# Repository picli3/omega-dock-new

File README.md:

# Omega dock\new con rele de estado solido a 220v @ 1A

Project released under CC-BY-SA 4.0 license  

1. [Project status](#project-status)  
1. [Project description](#project-description)  
1. [BOM](#bom)  
1. [Photos](#photos) 

If you want to discuss the project, join [the thread in the onion community forum](https://community.onion.io/topic/2284/my-omega-2-2-dock-new)

## Project status
v0.9 tested, working with some bodges  
v1.0 boards not tested yet, **proceed at your own risk**

## Project description 
This is my dock\new project: it's a small dock (same size as the mini dock and the omega) for the Onion Omega 2 and 2+.

I needed the smallest dock i could do, that featured:

* Ethernet
* Type A USB host
* Micro USB for power

It has an onboard linear voltage regulation (i didn't bother going with a switching one for such low power), magnetics integrated in the RJ45 connector to save space, USB host ESD protection (diode array), USB host PTC fuse.

On the left side there is the RJ45 connector and nothing on the back side of the board, so that you can easily access the MicroSD card on the Omega 2+.
On the right side (the antenna side of the omega) you have the USB type A connector, facing outwards, and the microusb connector for power, facing inwards.

The first version, v0.9, had some issues with the ethernet. Currently i've released v1.0 that solves all the issues, adds a led to check power and, making a better use of the space, the RJ45 connector doesn't protrude anymore. I haven't ordered the v1.0 PCBs yet, but the circuit is tested.

I've chosen 0805 passives, 1206 ptc fuse, big smd electrolitic caps, a SOT223 (the classic 1117) for power regulation and a SOT23-6 for usb host protection, so it can all be easily handsoldered with just a plain soldering iron. Probably the hardest part to handsolder is the SOT23-6 but it's easily doable by hand.

The components and board cost for the prototype it's arround 10 to 15€ per board.

## BOM
|    Symbol   |                 Package                | Quantity |    Valore   |                          Note                          |
|:-----------:|:--------------------------------------:|:--------:|:-----------:|:------------------------------------------------------:|
| C1          | CP_Elec_4x5.3                          |     1    | 10uF        | 10V or higher                                          |
| C2          | CP_Elec_6.3x5.3                        |     1    | 100uF       | 10V or higher                                          |
| C3, C4      | 0805                                   |     2    | 100nF       |                                                        |
| C5          | 0805                                   |     1    | 1uF         |                                                        |
| D1          | 1206                                   |     1    | PWR         | Amber LED                                              |
| F1          | 1206                                   |     1    | 1.5A        | PTC Fuse                                               |
| J1          | USB_A                                  |     1    | USB_A       | MOLEX 67643-3910                                       |
| J2          | USB_Micro-B                            |     1    | USB_PWR     | ADAM TECH MCR-AB1-S-RA-SMT-CS1-TR                      |
| J3          | RJ45_TRAFO_AMPHENOL                    |     1    | RJ45-TRAFO  | AMPHENOL LMJ1598824110DT39                             |
| R1,R2,R3,R4 | 0805                                   |     4    | 50R         | Ethernet termination resistors: should be 1% or better |
| R5          | 0805                                   |     1    | 150R        |                                                        |
| U1          | SOT23-6                                |     1    | USBLC6-2SC6 |                                                        |
| U2          | SOT223                                 |     1    | AP111733    |                                                        |
| U3          | Socket_Strip_Straight_1x16_Pitch2.00mm |     2    | OMEGA_2_2+  | Two 2mm 1x16 strip connectors                          |

## Photos

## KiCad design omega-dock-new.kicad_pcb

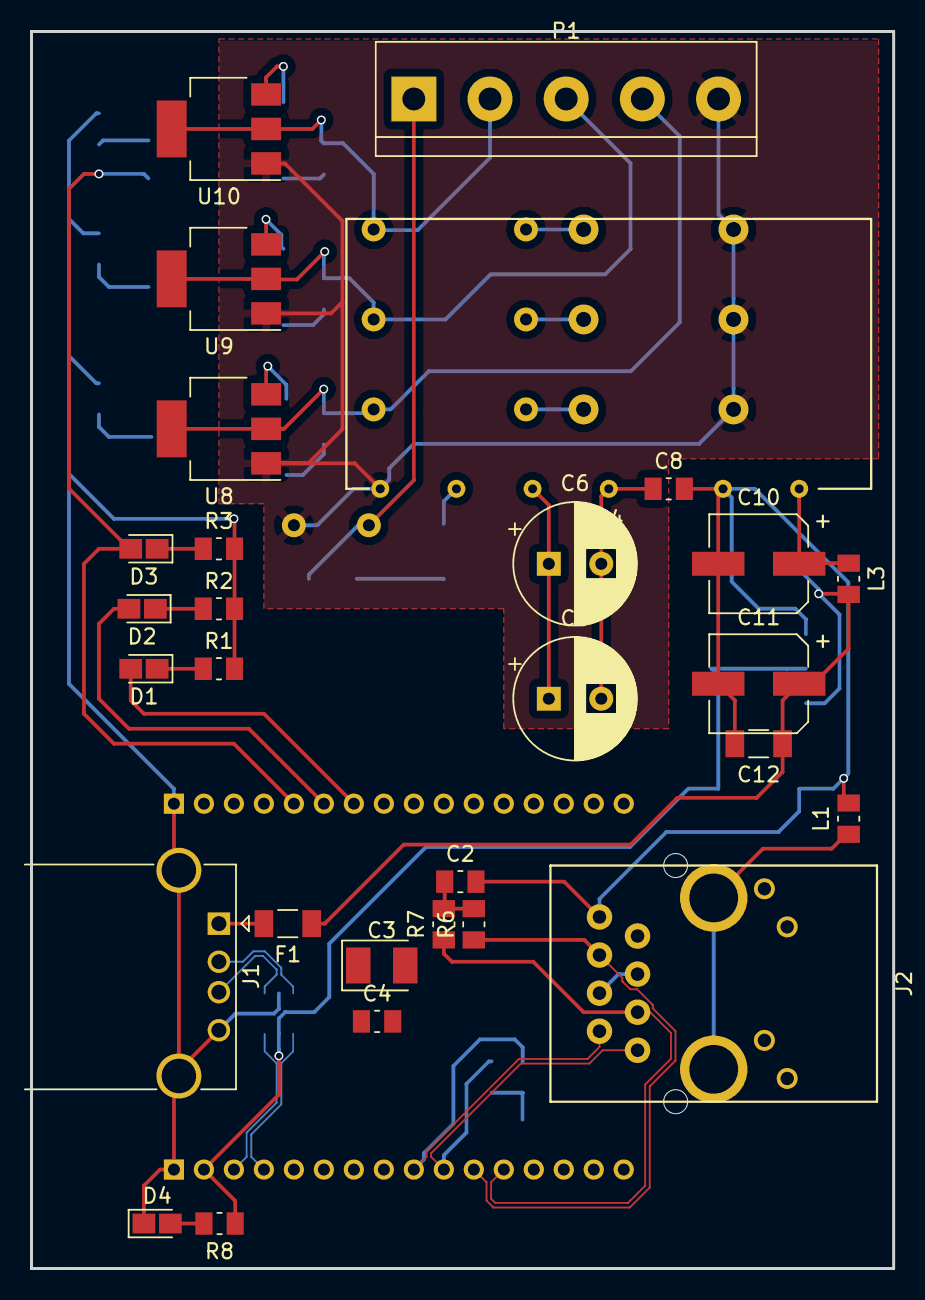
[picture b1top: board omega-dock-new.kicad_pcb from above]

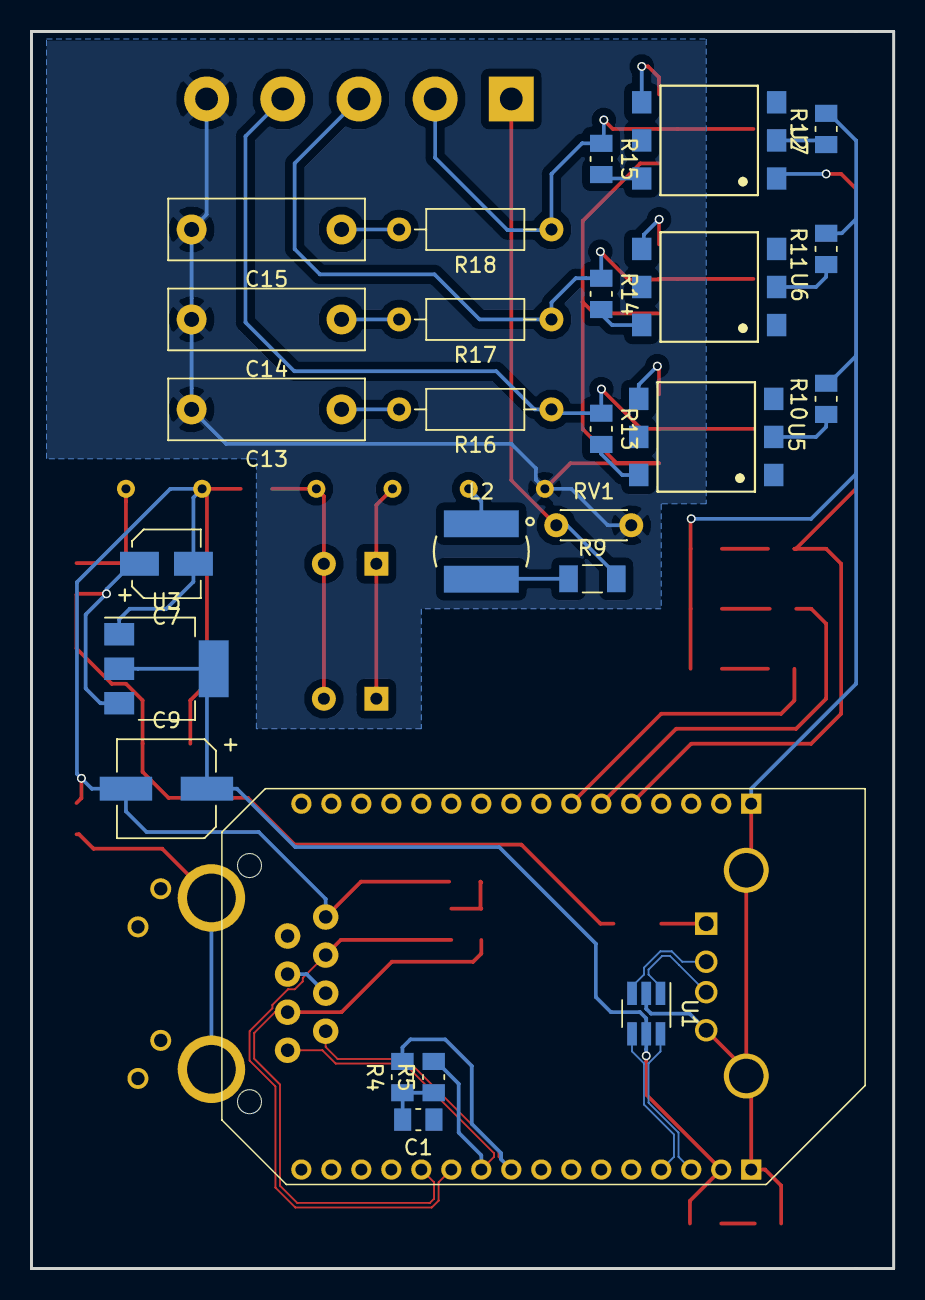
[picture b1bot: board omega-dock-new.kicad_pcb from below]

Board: 2 copper layers, 57.5 x 82.5 mm, 55 parts (26 on the bottom side), 45 nets.

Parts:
C1, C2: 100nF; C_0805_2012Metric_Pad1.15x1.50mm_HandSolder
C3: 47uF; CP_EIA-3528-12_Kemet-T_Pad1.63x2.40mm_HandSolder
C4, C8: 1nF; C_0805_2012Metric_Pad1.15x1.50mm_HandSolder
C5, C6: 4,7uF; CP_Radial_D8.0mm_P3.50mm
C7: 10uF; CP_Elec_4x5.3
C9: 100uF; CP_Elec_6.3x5.3
C10: 270uF; CP_Elec_6.3x7.7
C11: 68uF; CP_Elec_6.3x7.7
C12: 100nF; C_1206_3216Metric_Pad1.24x1.80mm_HandSolder
C13, C14, C15: 1nF; C_Rect_L13.0mm_W4.0mm_P10.00mm_FKS3_FKP3_MKS4
D1, D2, D3: LED; LED_0805_2012Metric_Castellated
D4: PWR; LED_0805_2012Metric_Castellated
F1: 1.5A; C_1206_3216Metric_Pad1.24x1.80mm_HandSolder
J1: USB_A; USB_A_Horizontal
J2: RJMG1BD3B8K1ANR; RJMG1B
L1: 220@100MHz; L_0805_2012Metric_Pad1.15x1.50mm_HandSolder
L2: SDR0503-472JL; SDR0503-XXX
L3: 74479776247; L_0805_2012Metric_Pad1.15x1.50mm_HandSolder
P1: POWER I/O; TerminalBlock_bornier-5_P5.08mm
R1, R2, R3: 220; R_0805_2012Metric_Pad1.15x1.50mm_HandSolder
R4, R5, R6, R7: 50R; R_0805_2012Metric_Pad1.15x1.50mm_HandSolder
R8: 150R; R_0805_2012Metric_Pad1.15x1.50mm_HandSolder
R9: 300k; R_1206_3216Metric_Pad1.24x1.80mm_HandSolder
R10, R11, R12, R13, R14, R15: 330; R_0805_2012Metric_Pad1.15x1.50mm_HandSolder
R16, R18: 33; R_Axial_DIN0207_L6.3mm_D2.5mm_P10.16mm_Horizontal
R17: 100; R_Axial_DIN0207_L6.3mm_D2.5mm_P10.16mm_Horizontal
RV1: B72214S0351K101; C_Disc_D4.3mm_W1.9mm_P5.00mm
U1: USBLC6-2; SOT-23-6_Handsoldering
U2: OMEGA_2
U3: AP111733; SOT-223
U4: PBO-3-S5
U5, U6, U7: MOC3063S-TA1; MOC306X
U8, U9, U10: Z0103MN 5AA4; SOT-223-Z01

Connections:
+3V3: C9.1, R8.1, U1.5, U2.31, U3.2, U3.4
+5V: C7.1, C11.1, C12.1, F1.1, L3.2, U3.3
/D+: U1.6, U2.30
/D-: U1.4, U2.29
/FuenteST/VO: C10.1, L3.1, U4.12
/OutTriac/Compresor: D3.2, U2.5, U7.1
/OutTriac/Resistencia: D1.2, U2.7, U6.1
/OutTriac/Ventilador: D2.2, U2.6, U5.1
/RX+: J2.3, R7.1, U2.21
/RX-: J2.6, R6.1, U2.22
/TX+: J2.1, R5.2, U2.23
/TX-: J2.2, R4.2, U2.24
/UD+: J1.3, U1.1
/UD-: J1.2, U1.3
CO: P1.2, R15.1, R18.1, U10.2
ETH_PWR: C3.1, C4.1, J2.4, J2.5, U2.25
GND: C1.1, C2.2, C3.2, C4.2, C7.2, C8.2, C9.2, C10.2, C11.2, C12.2, D4.1, J1.4, J1.5, J2.8, L1.2, R1.2, R2.2, R3.2, R10.2, R11.2, R12.2, U1.2, U2.1, U2.32, U3.1, U4.10
GNDREF: J2.SH, L1.1
Nac: C13.2, C14.2, C15.2, P1.5, RV1.2, U4.1, U8.1, U9.1, U10.1
unnamed: C1.2, R4.1, R5.1
unnamed: C2.1, R6.2, R7.2
unnamed: C5.1, C6.1, U4.5
unnamed: C5.2, C6.2, C8.1, U4.7
unnamed: C13.1, R16.2
unnamed: C14.1, R17.2
unnamed: C15.1, R18.2
unnamed: D1.1, R1.1
unnamed: D2.1, R2.1
unnamed: D3.1, R3.1
unnamed: D4.2, R8.2
unnamed: F1.2, J1.1
unnamed: L2.1, R9.1
unnamed: L2.2, U4.3
unnamed: R10.1, U5.2
unnamed: R11.1, U6.2
unnamed: R12.1, U7.2
unnamed: R13.2, U5.6
unnamed: R14.2, U6.6
unnamed: R15.2, U7.6
unnamed: U5.4, U8.3
unnamed: U6.4, U9.3
unnamed: U7.4, U10.3
RE: P1.3, R14.1, R17.1, U9.2
VE: P1.4, R13.1, R16.1, U8.2
Vac: P1.1, R9.2, RV1.1

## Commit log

2018-03-03 ajustando a kicad 5
2018-03-03 redimencioando unas cosas
2018-03-05 actualizando todos los perifericos
2018-03-05 limpiando

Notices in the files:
README.md:
License: CC BY-SA 4.0
